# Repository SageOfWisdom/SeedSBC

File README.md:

# SeedSBC

## ICE40HX8K FPGA development board.

## Latest Revision: 
* [SeedSBC rev2.0](hardware/rev2.0/)

Previous Revisions:
* [SeedSBC rev1.1](hardware/rev1.1/)
* [SeedSBC rev1.0](hardware/rev1.0/)

---

## What is it?
This is an Open Source Hardware single board computer and development board implementing the Lattice ICE40 FPGA. The board features regular I/O breakout pins, an SRAM unit, and a microSD MMC connector. The footprint is reminiscent of other "Altoids Tin" format SBCs.

## Hardware Overview
* Lattice ICE40HX8K FPGA in 121-Ball caBGA package

    * 7,680 - Logic Cells (LUT + Flip-Flop)
    * 32 - RAM4K Memory Blocks
    * 128k - RAM4K RAM bits
    * 2 - PLLs
    * 106 - Programmable I/O Pins
    * 13 - Differential Input Pairs
* SRAM Memory
    * 
* USB-C connection
    * 
* Non-Volatile Memory
    * asdf 
        * asdf
    * MicroSD socket
        * 4bit SD interface (CK, CMD, DAT0-3)
* Power supply
    * Battery charger (100mA), with LED charge indicators
    * Li-Ion battery connector
* 48MHz onboard oscillator
* Accessible 0.1" 2-wire SPI NVM programming breakout
* User I/O
    * 1x Button 
    * 1x RGB LED
    * 18x I/O on 0.1" headers
* Board Format
    * Dimensions: 86.36mm x 53.34mm (3.4" x 2.1")
    * 4x 2.2mm plated mounting holes
---

## Example code
Example code for Verilog, And RiscV AVR can be found here:

* [ToDo]()

## Licence

 * None

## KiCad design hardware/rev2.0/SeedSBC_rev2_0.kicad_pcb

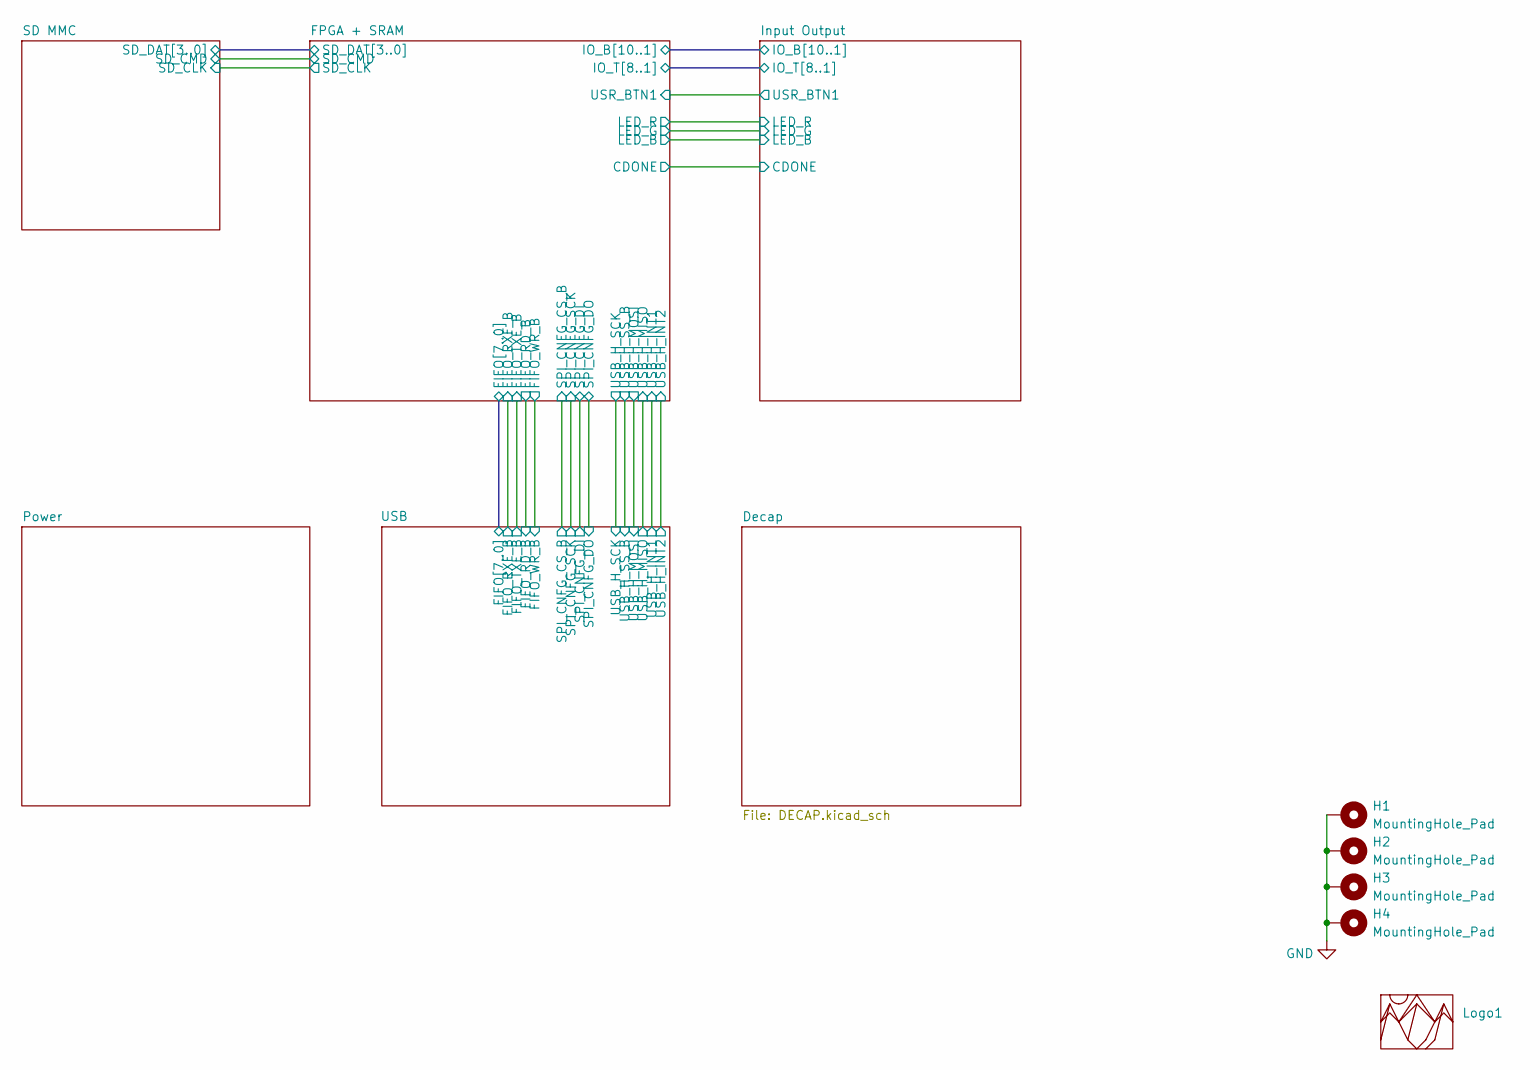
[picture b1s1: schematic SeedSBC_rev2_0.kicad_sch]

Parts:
H1, H2, H3, H4: MountingHole_Pad; MountingHole_2.2mm_M2_Pad_Via
Logo1: seeds

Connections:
GND: H1.1, H2.1, H3.1, H4.1; also elsewhere on the board

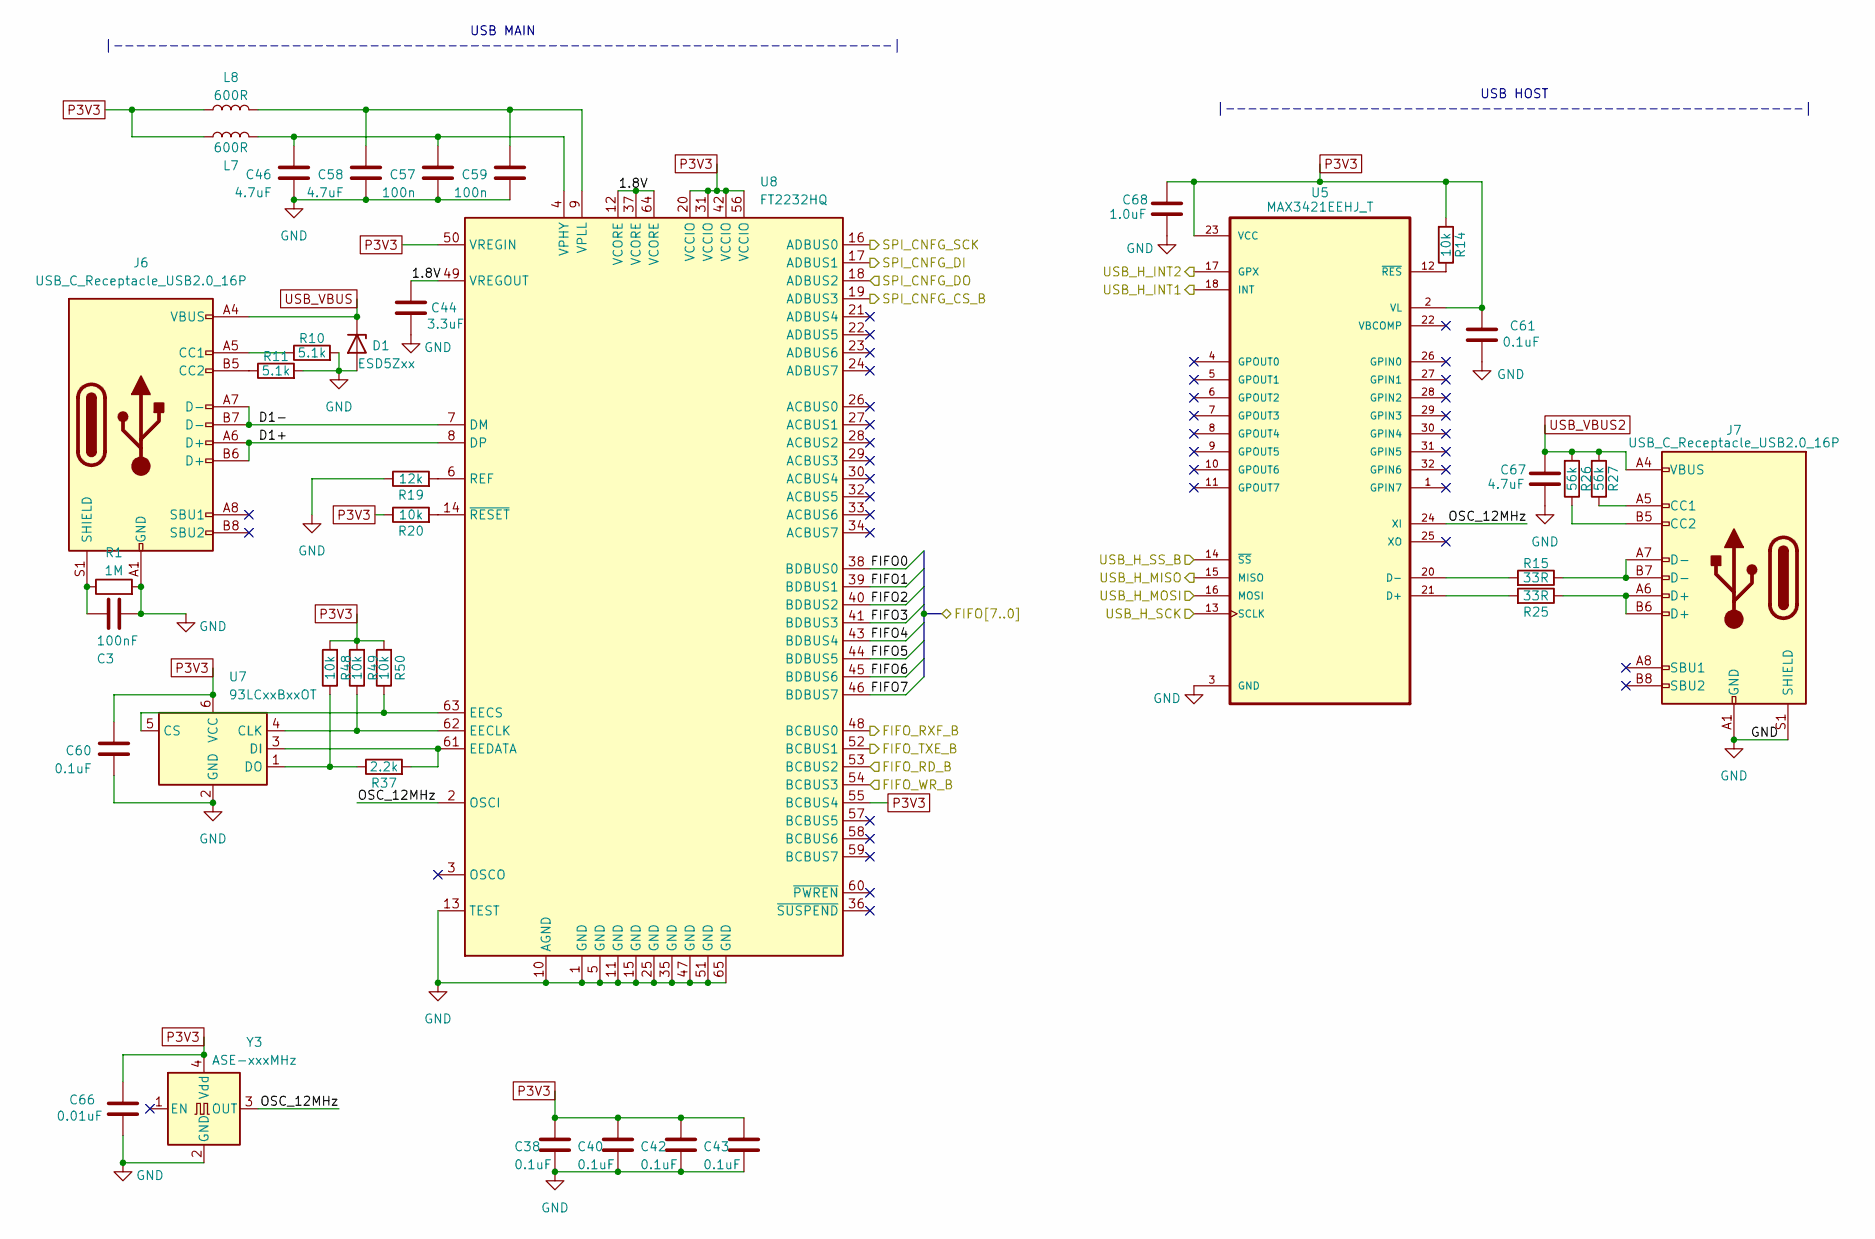
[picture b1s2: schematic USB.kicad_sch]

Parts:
C3: 100nF; C_0603_1608Metric
C38, C40, C42, C43, C60, C61: 0.1uF; C_0603_1608Metric
C44: 3.3uF; C_0603_1608Metric
C46, C58, C67: 4.7uF; C_0603_1608Metric
C57, C59: 100n; C_0603_1608Metric
C66: 0.01uF; C_0603_1608Metric
C68: 1.0uF; C_0603_1608Metric
D1: ESD5Zxx; D_SOD-523
J6, J7: USB_C_Receptacle_USB2.0_16P; USB_C_Receptacle_GCT_USB4105-xx-A_16P_TopMnt_Horizontal
L7, L8: 600R; L_0603_1608Metric
R1: 1M; R_0603_1608Metric
R10, R11: 5.1k; R_0603_1608Metric
R14, R20, R48, R49, R50: 10k; R_0603_1608Metric
R15, R25: 33R; R_0603_1608Metric
R19: 12k; R_0603_1608Metric
R26, R27: 56k; R_0603_1608Metric
R37: 2.2k; R_0603_1608Metric
U5: MAX3421EEHJ_T; QFP50P700X700X120-32N
U7: 93LCxxBxxOT; SOT-23-6
U8: FT2232HQ; QFN-64-1EP_9x9mm_P0.5mm_EP4.35x4.35mm
Y3: ASE-xxxMHz; Oscillator_SMD_Abracon_ASE-4Pin_3.2x2.5mm

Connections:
/FPGA + SRAM/FIFO0: U8.38 (BDBUS0); also elsewhere on the board
/FPGA + SRAM/FIFO1: U8.39 (BDBUS1); also elsewhere on the board
/FPGA + SRAM/FIFO2: U8.40 (BDBUS2); also elsewhere on the board
/FPGA + SRAM/FIFO3: U8.41 (BDBUS3); also elsewhere on the board
/FPGA + SRAM/FIFO4: U8.43 (BDBUS4); also elsewhere on the board
/FPGA + SRAM/FIFO5: U8.44 (BDBUS5); also elsewhere on the board
/FPGA + SRAM/FIFO6: U8.45 (BDBUS6); also elsewhere on the board
/FPGA + SRAM/FIFO7: U8.46 (BDBUS7); also elsewhere on the board
/FPGA + SRAM/FIFO_RD_B: U8.53 (BCBUS2); also elsewhere on the board
/FPGA + SRAM/FIFO_RXF_B: U8.48 (BCBUS0); also elsewhere on the board
/FPGA + SRAM/FIFO_TXE_B: U8.52 (BCBUS1); also elsewhere on the board
/FPGA + SRAM/FIFO_WR_B: U8.54 (BCBUS3); also elsewhere on the board
/FPGA + SRAM/FPGA/SPI_CNFG_DI: U8.17 (ADBUS1); also elsewhere on the board
/FPGA + SRAM/FPGA/SPI_CNFG_DO: U8.18 (ADBUS2); also elsewhere on the board
/FPGA + SRAM/FPGA/SPI_CNFG_SCK: U8.16 (ADBUS0); also elsewhere on the board
/FPGA + SRAM/SPI_CNFG_CS_B: U8.19 (ADBUS3); also elsewhere on the board
/FPGA + SRAM/USB_H_INT1: U5.18 (INT); also elsewhere on the board
/FPGA + SRAM/USB_H_INT2: U5.17 (GPX); also elsewhere on the board
/FPGA + SRAM/USB_H_MISO: U5.15 (MISO); also elsewhere on the board
/FPGA + SRAM/USB_H_MOSI: U5.16 (MOSI); also elsewhere on the board
/FPGA + SRAM/USB_H_SCK: U5.13 (SCLK); also elsewhere on the board
/FPGA + SRAM/USB_H_SS_B: U5.14 (~SS); also elsewhere on the board
/USB/1.8V: C44.1, U8.12 (VCORE), U8.37 (VCORE), U8.49 (VREGOUT), U8.64 (VCORE)
/USB/D1+: J6.A6 (D+), J6.B6 (D+), U8.8 (DP)
/USB/D1-: J6.A7 (D-), J6.B7 (D-), U8.7 (DM)
/USB/OSC_12MHz: U5.24 (XI), U8.2 (OSCI), Y3.3 (OUT)
GND: C3.2, C38.2, C40.2, C42.2, C43.2, C44.2, C46.2, C57.2, C58.2, C59.2, C60.2, C61.2, C66.2, C67.2, C68.2, D1.2 (A), J6.A1 (GND), J6.A12 (GND), J6.B1 (GND), J6.B12 (GND), J7.A1 (GND), J7.A12 (GND), J7.B1 (GND), J7.B12 (GND), J7.S1 (SHIELD), R1.2, R10.2, R11.2, R19.1, U5.3 (GND), U5.19 (GND), U7.2 (GND), U8.1 (GND), U8.5 (GND), U8.10 (AGND), U8.11 (GND), U8.13 (TEST), U8.15 (GND), U8.25 (GND), U8.35 (GND), U8.47 (GND), U8.51 (GND), U8.65 (GND), Y3.2 (GND); also elsewhere on the board
unnamed: J6.A5 (CC1), R10.1
unnamed: J6.B5 (CC2), R11.1
unnamed: C3.1, J6.S1 (SHIELD), R1.1
unnamed: J7.A5 (CC1), R27.1
unnamed: J7.B5 (CC2), R26.1
unnamed: J7.A6 (D+), J7.B6 (D+), R25.1
unnamed: J7.A7 (D-), J7.B7 (D-), R15.1
unnamed: R25.2, U5.21 (D+)
unnamed: R15.2, U5.20 (D-)
unnamed: R14.1, U5.12 (~RES)
unnamed: R49.1, U7.4 (CLK), U8.62 (EECLK)
unnamed: R50.1, U7.5 (CS), U8.63 (EECS)
unnamed: R37.2, U7.3 (DI), U8.61 (EEDATA)
unnamed: R37.1, R48.1, U7.1 (DO)
unnamed: R19.2, U8.6 (REF)
unnamed: C46.1, C57.1, L7.2, U8.4 (VPHY)
unnamed: C58.1, C59.1, L8.2, U8.9 (VPLL)
unnamed: R20.2, U8.14 (~RESET)
USB_VBUS: D1.1 (K), J6.A4 (VBUS), J6.A9 (VBUS), J6.B4 (VBUS), J6.B9 (VBUS); also elsewhere on the board

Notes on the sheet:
USB HOST |----------------------------------------------------|
USB MAIN |----------------------------------------------------------------------|

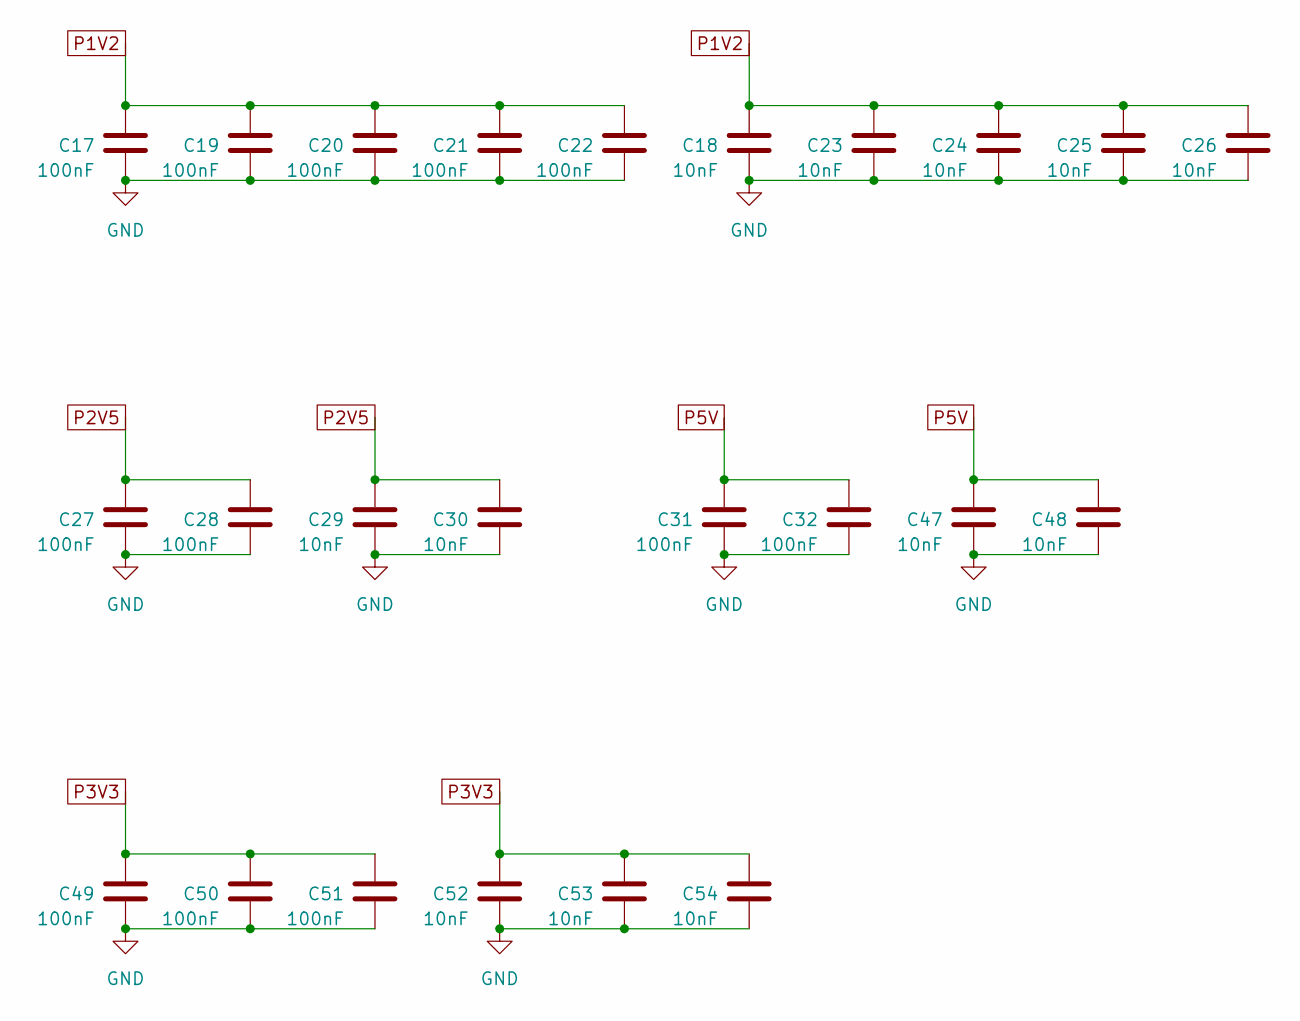
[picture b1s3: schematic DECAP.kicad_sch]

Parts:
C17, C19, C20, C21, C22, C27, C28, C31, C32, C49, C50, C51: 100nF
C18, C23, C24, C25, C26, C29, C30, C47, C48, C52, C53, C54: 10nF

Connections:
GND: C17.2, C18.2, C19.2, C20.2, C21.2, C22.2, C23.2, C24.2, C25.2, C26.2, C27.2, C28.2, C29.2, C30.2, C31.2, C32.2, C47.2, C48.2, C49.2, C50.2, C51.2, C52.2, C53.2, C54.2; also elsewhere on the board
P1V2: C17.1, C18.1, C19.1, C20.1, C21.1, C22.1, C23.1, C24.1, C25.1, C26.1; also elsewhere on the board
P2V5: C27.1, C28.1, C29.1, C30.1; also elsewhere on the board

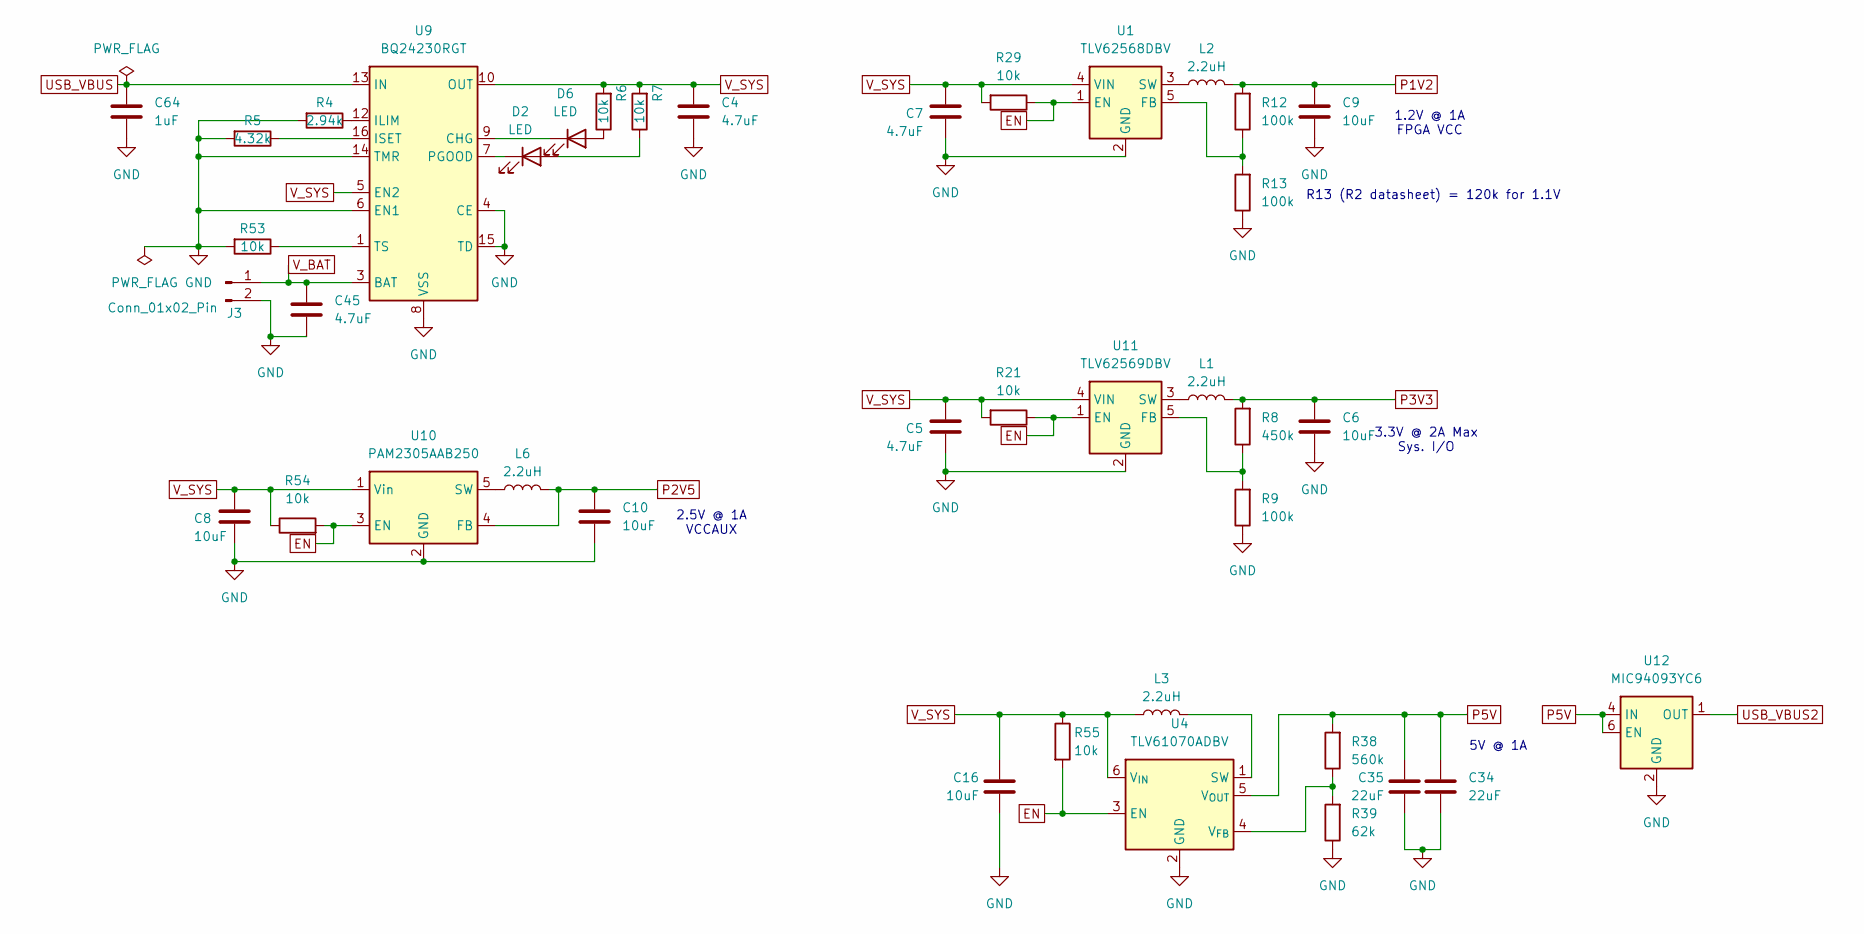
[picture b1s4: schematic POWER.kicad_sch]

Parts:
C4, C5, C7, C45: 4.7uF; C_0603_1608Metric
C6, C8, C9, C10, C16: 10uF; C_0603_1608Metric
C34, C35: 22uF; C_0603_1608Metric
C64: 1uF; C_0603_1608Metric
D2, D6: LED; LED_0603_1608Metric
J3: Conn_01x02_Pin; JST_PH_B2B-PH-K_1x02_P2.00mm_Vertical
L1, L2, L3: 2.2uH; L_Neosid_SMS-ME3010
L6: 2.2uH; L_0603_1608Metric
R4: 2.94k; R_0603_1608Metric
R5: 4.32k; R_0603_1608Metric
R6, R7, R21, R29, R53, R54, R55: 10k; R_0603_1608Metric
R8: 450k; R_0603_1608Metric
R9, R12, R13: 100k; R_0603_1608Metric
R38: 560k; R_0603_1608Metric
R39: 62k; R_0603_1608Metric
U1: TLV62568DBV; SOT-23-5
U4: TLV61070ADBV; SOT-23-6
U9: BQ24230RGT; VQFN-16-1EP_3x3mm_P0.5mm_EP1.68x1.68mm_ThermalVias
U10: PAM2305AAB250; TSOT-23-5
U11: TLV62569DBV; SOT-23-5
U12: MIC94093YC6; SOT-363_SC-70-6

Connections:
EN: R21.1, R29.1, R54.2, R55.2, U1.1 (EN), U4.3 (EN), U10.3 (EN), U11.1 (EN); also elsewhere on the board
GND: C4.2, C5.2, C6.2, C7.2, C8.2, C9.2, C10.2, C16.2, C34.2, C35.2, C45.2, C64.2, J3.2, R4.2, R5.2, R9.1, R13.1, R39.1, R53.2, U1.2 (GND), U4.2 (GND), U9.4 (CE), U9.6 (EN1), U9.8 (VSS), U9.14 (TMR), U9.15 (TD), U9.17 (VSS), U10.2 (GND), U11.2 (GND), U12.2 (GND), U12.5 (GND); also elsewhere on the board
unnamed: D2.2 (A), R7.1
unnamed: D2.1 (K), U9.7 (PGOOD)
unnamed: D6.2 (A), R6.1
unnamed: D6.1 (K), U9.9 (CHG)
unnamed: R12.1, R13.2, U1.5 (FB)
unnamed: L2.1, U1.3 (SW)
unnamed: L3.2, U4.1 (SW)
unnamed: R38.1, R39.2, U4.4 (V_{FB})
unnamed: R4.1, U9.12 (ILIM)
unnamed: R5.1, U9.16 (ISET)
unnamed: R53.1, U9.1 (TS)
unnamed: L6.1, U10.5 (SW)
unnamed: R8.1, R9.2, U11.5 (FB)
unnamed: L1.1, U11.3 (SW)
P1V2: C9.1, L2.2, R12.2; also elsewhere on the board
P2V5: C10.1, L6.2, U10.4 (FB); also elsewhere on the board
P5V: C34.1, C35.1, R38.2, U4.5 (V_{OUT}), U12.4 (IN), U12.6 (EN)
USB_VBUS: C64.1, U9.13 (IN); also elsewhere on the board
V_BAT: C45.1, J3.1, U9.2 (BAT), U9.3 (BAT); also elsewhere on the board
V_SYS: C4.1, C5.1, C7.1, C8.1, C16.1, L3.1, R6.2, R7.2, R21.2, R29.2, R54.1, R55.1, U1.4 (VIN), U4.6 (V_{IN}), U9.5 (EN2), U9.10 (OUT), U9.11 (OUT), U10.1 (VI), U11.4 (VIN)

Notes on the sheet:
5V @ 1A
2.5V @ 1A VCCAUX
3.3V @ 2A Max Sys. I/O
R13 (R2 datasheet) = 120k for 1.1V
1.2V @ 1A FPGA VCC

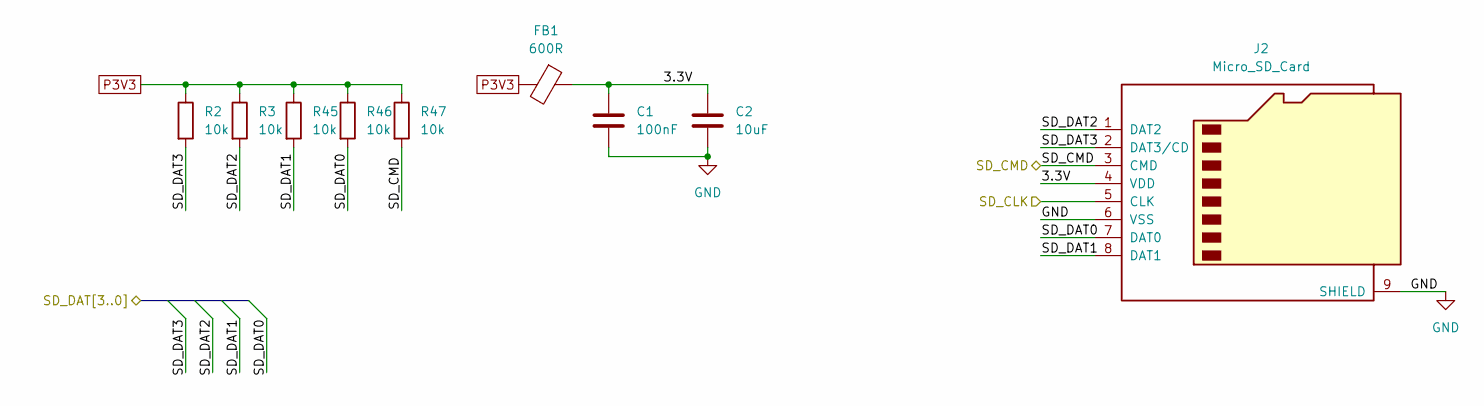
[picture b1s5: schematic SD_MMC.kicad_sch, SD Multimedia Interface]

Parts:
C1: 100nF; C_0603_1608Metric
C2: 10uF; C_0603_1608Metric
FB1: 600R; C_0603_1608Metric
J2: Micro_SD_Card; microSD_HC_Hirose_DM3BT-DSF-PEJS
R2, R3, R45, R46, R47: 10k; R_0603_1608Metric

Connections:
/FPGA + SRAM/SD_CLK: J2.5 (CLK); also elsewhere on the board
/FPGA + SRAM/SD_DAT0: J2.7 (DAT0), R46.2; also elsewhere on the board
/FPGA + SRAM/SD_DAT1: J2.8 (DAT1), R45.2; also elsewhere on the board
/FPGA + SRAM/SD_DAT2: J2.1 (DAT2), R3.2; also elsewhere on the board
/FPGA + SRAM/SD_DAT3: J2.2 (DAT3/CD), R2.2; also elsewhere on the board
/SD MMC/SD_CMD: J2.3 (CMD), R47.2; also elsewhere on the board
GND: C1.2, C2.2, J2.6 (VSS), J2.9 (SHIELD); also elsewhere on the board

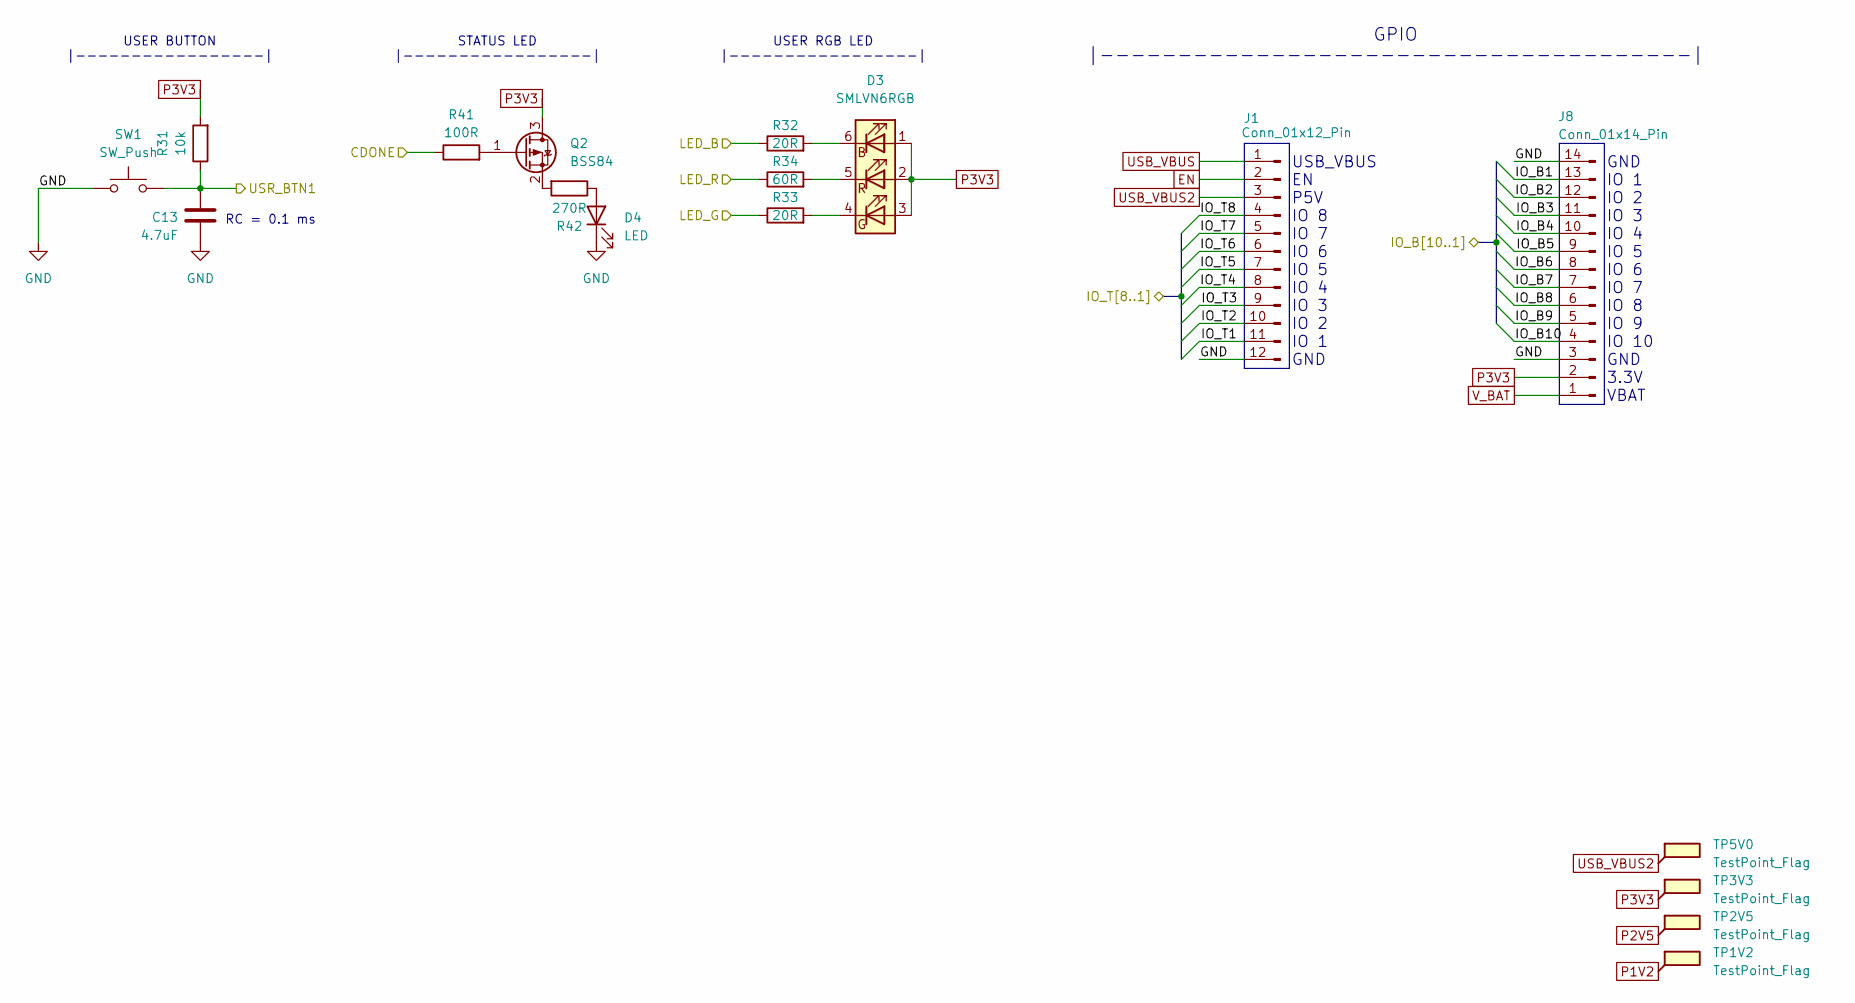
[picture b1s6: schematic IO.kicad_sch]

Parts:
C13: 4.7uF; C_0603_1608Metric
D3: SMLVN6RGB; LED_ROHM_SMLVN6
D4: LED; LED_0603_1608Metric
J1: Conn_01x12_Pin; PinHeader_1x12_P2.54mm_Vertical
J8: Conn_01x14_Pin; PinHeader_1x14_P2.54mm_Vertical
Q2: BSS84; SOT-23
R31: 10k; R_0603_1608Metric
R32, R33: 20R; R_0603_1608Metric
R34: 60R; R_0603_1608Metric
R41: 100R; R_0603_1608Metric
R42: 270R; R_0603_1608Metric
SW1: SW_Push; SW_SPST_CK_RS282G05A3
TP1V2, TP2V5, TP3V3, TP5V0: TestPoint_Flag; TestPoint_Pad_D1.0mm

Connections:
/FPGA + SRAM/CDONE: R41.1; also elsewhere on the board
/FPGA + SRAM/IO_B1: J8.13; also elsewhere on the board
/FPGA + SRAM/IO_B2: J8.12; also elsewhere on the board
/FPGA + SRAM/IO_B3: J8.11; also elsewhere on the board
/FPGA + SRAM/IO_B4: J8.10; also elsewhere on the board
/FPGA + SRAM/IO_B5: J8.9; also elsewhere on the board
/FPGA + SRAM/IO_B6: J8.8; also elsewhere on the board
/FPGA + SRAM/IO_B7: J8.7; also elsewhere on the board
/FPGA + SRAM/IO_B8: J8.6; also elsewhere on the board
/FPGA + SRAM/IO_B9: J8.5; also elsewhere on the board
/FPGA + SRAM/IO_B10: J8.4; also elsewhere on the board
/FPGA + SRAM/IO_T1: J1.11; also elsewhere on the board
/FPGA + SRAM/IO_T2: J1.10; also elsewhere on the board
/FPGA + SRAM/IO_T3: J1.9; also elsewhere on the board
/FPGA + SRAM/IO_T4: J1.8; also elsewhere on the board
/FPGA + SRAM/IO_T5: J1.7; also elsewhere on the board
/FPGA + SRAM/IO_T6: J1.6; also elsewhere on the board
/FPGA + SRAM/IO_T7: J1.5; also elsewhere on the board
/FPGA + SRAM/IO_T8: J1.4; also elsewhere on the board
/FPGA + SRAM/LED_B: R32.1; also elsewhere on the board
/FPGA + SRAM/LED_G: R33.1; also elsewhere on the board
/FPGA + SRAM/LED_R: R34.1; also elsewhere on the board
/FPGA + SRAM/USR_BTN1: C13.1, R31.1, SW1.2; also elsewhere on the board
EN: J1.2; also elsewhere on the board
GND: C13.2, D4.1 (K), J1.12, J8.3, J8.14, SW1.1; also elsewhere on the board
unnamed: D3.6 (BK), R32.2
unnamed: D3.4 (GK), R33.2
unnamed: D3.5 (RK), R34.2
unnamed: D4.2 (A), R42.1
unnamed: Q2.1 (G), R41.2
unnamed: Q2.2 (S), R42.2
P1V2: TP1V2.1; also elsewhere on the board
P2V5: TP2V5.1; also elsewhere on the board
USB_VBUS: J1.1; also elsewhere on the board
V_BAT: J8.1; also elsewhere on the board

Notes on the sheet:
USER RGB LED |-----------------|
USER BUTTON |-----------------|
GPIO |--------------------------------------|
GND IO 1 IO 2 IO 3 IO 4 IO 5 IO 6 IO 7 IO 8 IO 9 IO 10 GND 3.3V VBAT
RC = 0.1 ms
USB_VBUS EN P5V IO 8 IO 7 IO 6 IO 5 IO 4 IO 3 IO 2 IO 1 GND
STATUS LED |-----------------|
